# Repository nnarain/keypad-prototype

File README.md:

# Keypad prototype

This is a prototype macro keypad. It's based on an Arduino Pro Micro (The version from Sparkfun). It also has room for
and OLED display (over I2C).

The design is a simple key matrix with diodes and should be easily extendable to a full sized keyboard.

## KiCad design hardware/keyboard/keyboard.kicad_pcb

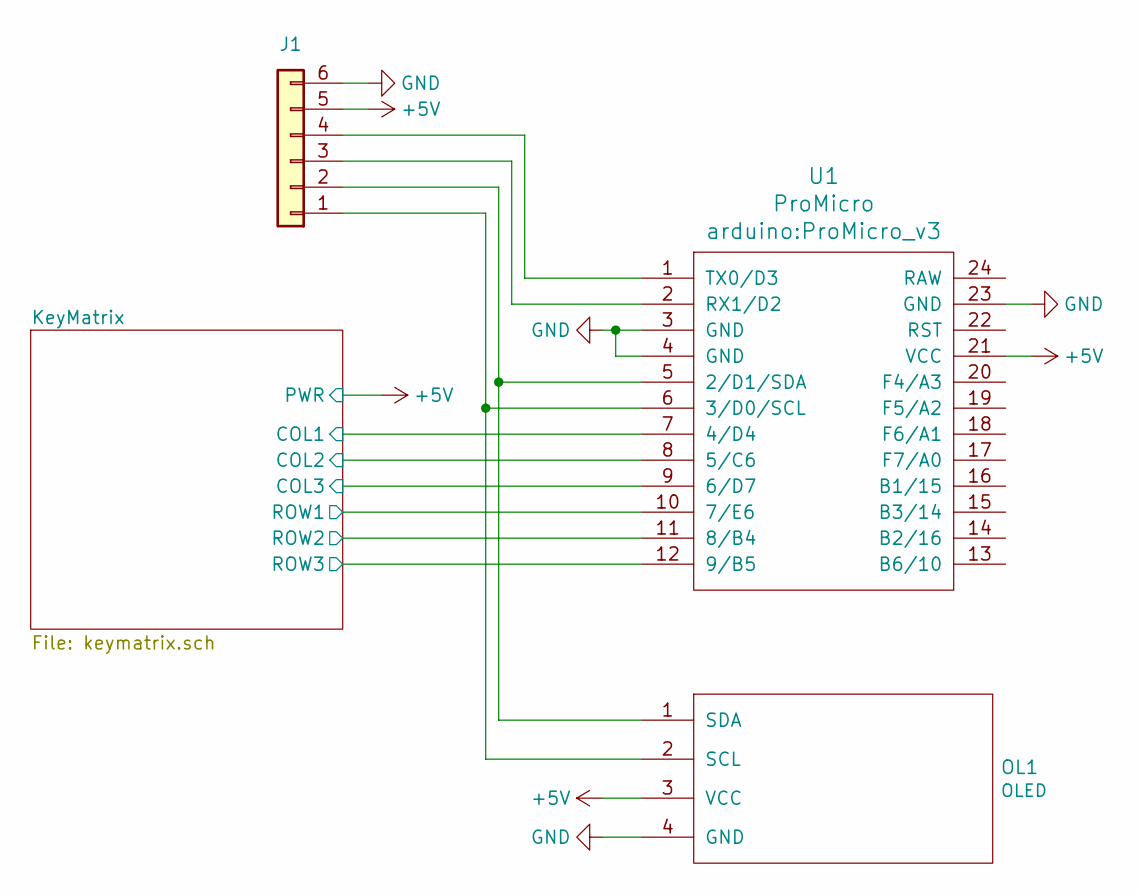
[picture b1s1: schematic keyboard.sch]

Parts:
J1: Conn_01x06; PinSocket_1x06_P2.54mm_Vertical
OL1: OLED; OLED_v2
U1: ProMicro; ProMicro_v3

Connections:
+5V: J1.5, OL1.3 (VCC), U1.21 (VCC); also elsewhere on the board
/KeyMatrix/COL1: U1.7 (4/D4); also elsewhere on the board
/KeyMatrix/COL2: U1.8 (5/C6); also elsewhere on the board
/KeyMatrix/COL3: U1.9 (6/D7); also elsewhere on the board
/KeyMatrix/ROW1: U1.10 (7/E6); also elsewhere on the board
/KeyMatrix/ROW2: U1.11 (8/B4); also elsewhere on the board
/KeyMatrix/ROW3: U1.12 (9/B5); also elsewhere on the board
GND: J1.6, OL1.4 (GND), U1.3 (GND), U1.4 (GND), U1.23 (GND)
unnamed: J1.1, OL1.2 (SCL), U1.6 (3/D0/SCL)
unnamed: J1.2, OL1.1 (SDA), U1.5 (2/D1/SDA)
unnamed: J1.3, U1.2 (RX1/D2)
unnamed: J1.4, U1.1 (TX0/D3)

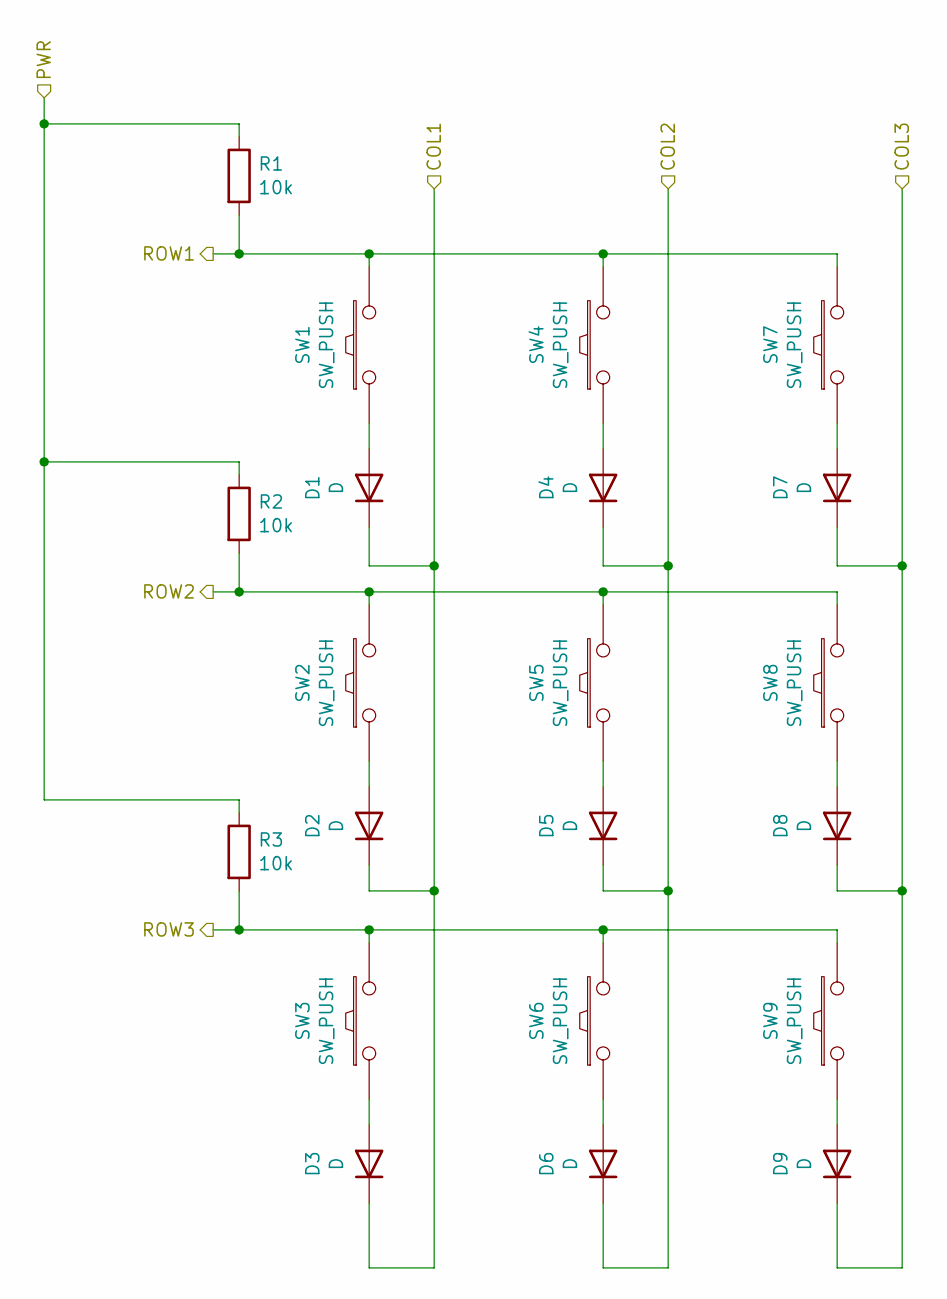
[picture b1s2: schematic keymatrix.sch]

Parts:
D1, D2, D3, D4, D5, D6, D7, D8, D9: D; D_DO-41_SOD81_P7.62mm_Horizontal
R1, R2, R3: 10k; R_Axial_DIN0204_L3.6mm_D1.6mm_P5.08mm_Horizontal
SW1, SW2, SW3, SW4, SW5, SW6, SW7, SW8, SW9: SW_PUSH; CherryMX_1u

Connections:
+5V: R1.1, R2.1, R3.1; also elsewhere on the board
/KeyMatrix/COL1: D1.1 (K), D2.1 (K), D3.1 (K); also elsewhere on the board
/KeyMatrix/COL2: D4.1 (K), D5.1 (K), D6.1 (K); also elsewhere on the board
/KeyMatrix/COL3: D7.1 (K), D8.1 (K), D9.1 (K); also elsewhere on the board
/KeyMatrix/ROW1: R1.2, SW1.2, SW4.2, SW7.2; also elsewhere on the board
/KeyMatrix/ROW2: R2.2, SW2.2, SW5.2, SW8.2; also elsewhere on the board
/KeyMatrix/ROW3: R3.2, SW3.2, SW6.2, SW9.2; also elsewhere on the board
unnamed: D1.2 (A), SW1.1
unnamed: D2.2 (A), SW2.1
unnamed: D3.2 (A), SW3.1
unnamed: D4.2 (A), SW4.1
unnamed: D5.2 (A), SW5.1
unnamed: D6.2 (A), SW6.1
unnamed: D7.2 (A), SW7.1
unnamed: D8.2 (A), SW8.1
unnamed: D9.2 (A), SW9.1

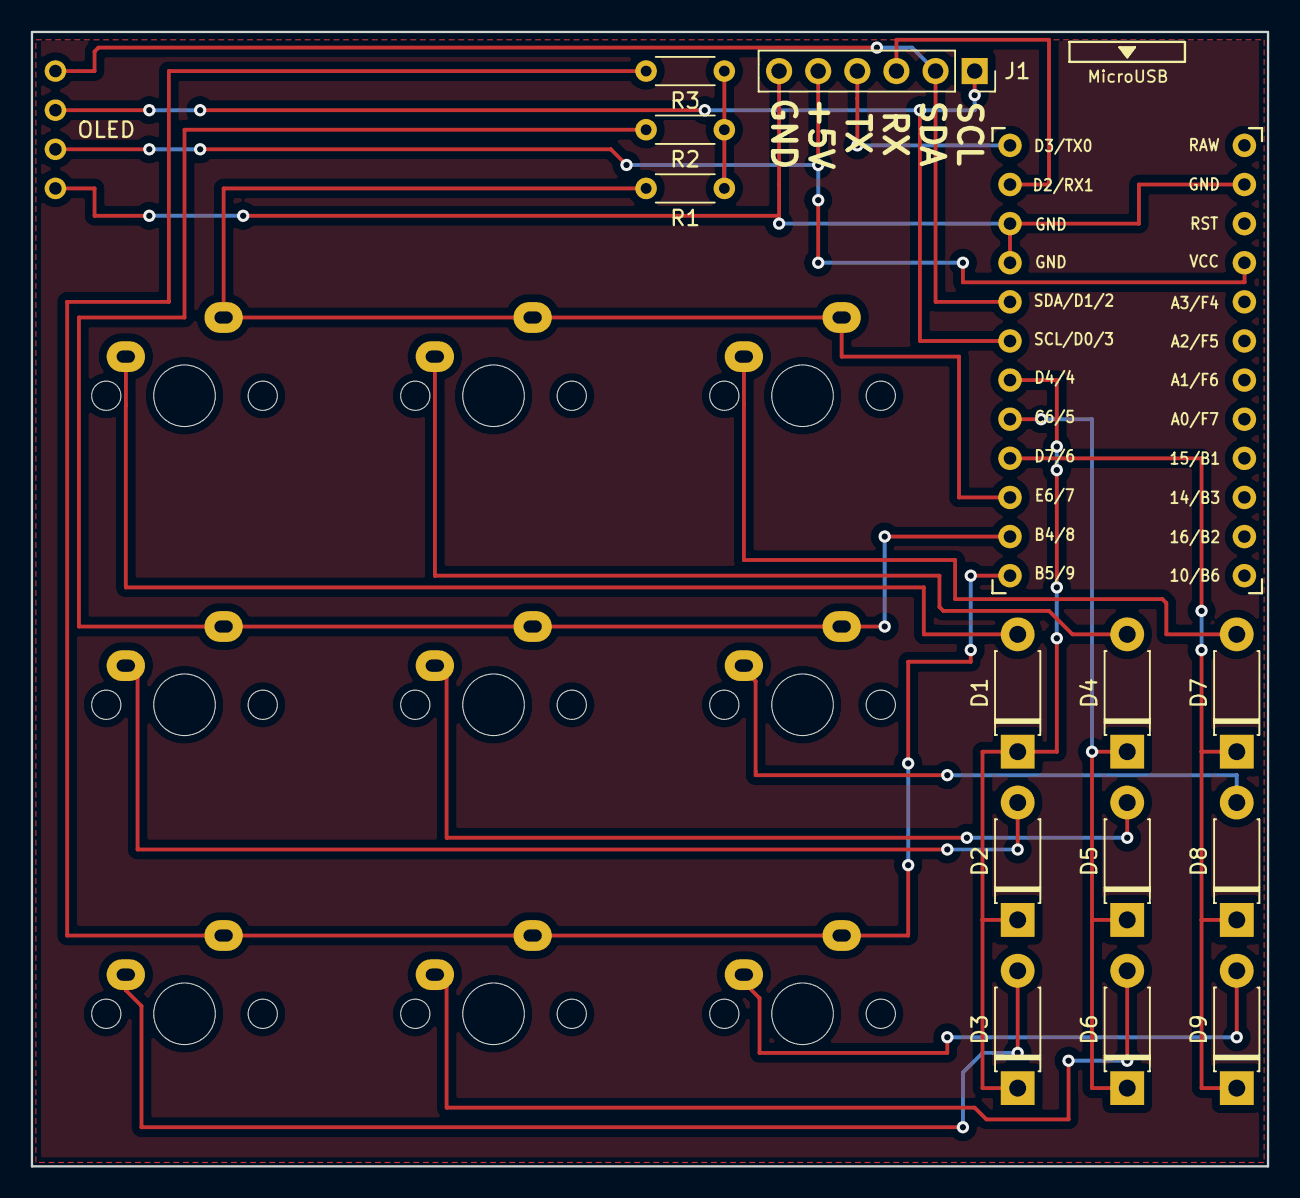
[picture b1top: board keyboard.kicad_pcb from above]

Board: 2 copper layers, 80.3 x 73.7 mm, 24 parts (0 on the bottom side), 21 nets.

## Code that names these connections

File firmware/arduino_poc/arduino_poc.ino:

/**
  POC Firmware for macro keypad
  @author Natesh Narain <nnaraindev@gmail.com>
*/

#include <Keyboard.h>

#define COL1 4
#define COL2 5
#define COL3 6
#define NUM_COLS 3

#define ROW1 7
#define ROW2 8
#define ROW3 9
#define NUM_ROWS 3

static const int COL_PINS[NUM_COLS] = {COL1, COL2, COL3};
static const int ROW_PINS[NUM_ROWS] = {ROW1, ROW2, ROW3};

static const char BUTTONS[NUM_COLS][NUM_ROWS] = { {'7', '4', '1'}, {'8', '5', '2'}, {'9', '6', '3'} };

void setup() {
  //pinMode(COL1, OUTPUT);
  //pinMode(ROW1, INPUT);

  for (int i = 0; i < NUM_COLS; ++i)
  {
    pinMode(COL_PINS[i], OUTPUT);
  }

  for (int i = 0; i < NUM_COLS; ++i)
  {
    pinMode(ROW_PINS[i], INPUT);
  }

  Serial.begin(115200);
  Keyboard.begin();
}

void loop() {
  for (int col = 0; col < NUM_COLS; ++col)
  {
    // Select the column by pulling it LOW
    digitalWrite(COL_PINS[col], LOW);

    for (int row = 0; row < NUM_ROWS; ++row)
    {
      // Button pressed are a LOW signal
      if (digitalRead(ROW_PINS[row]) == LOW)
      {
        Keyboard.press(BUTTONS[col][row]);
      }
      else
      {
        Keyboard.release(BUTTONS[col][row]);
      }
    }

    //De-select column
    digitalWrite(COL_PINS[col], HIGH);
  }
}

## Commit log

2020-11-18 Initial Keypad prototype
2021-02-24 update gitignore
2021-02-25 Update ProMicro footprint
2021-02-27 Added firmware project
2021-03-20 Fixed broken connections in hierarchy
2021-03-20 Added Arduino keymatrix test
2021-03-21 Do keyboard presses
2021-03-21 Resolves #1. Docs and CI
2021-03-21 Explicity add _generated folder
2021-03-21 rename pdf
2021-03-21 deploy: 33331ed97197af4d176c2f339ab7879f0a1cb078
